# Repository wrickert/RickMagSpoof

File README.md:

This is my variant of the MagSpoof Project

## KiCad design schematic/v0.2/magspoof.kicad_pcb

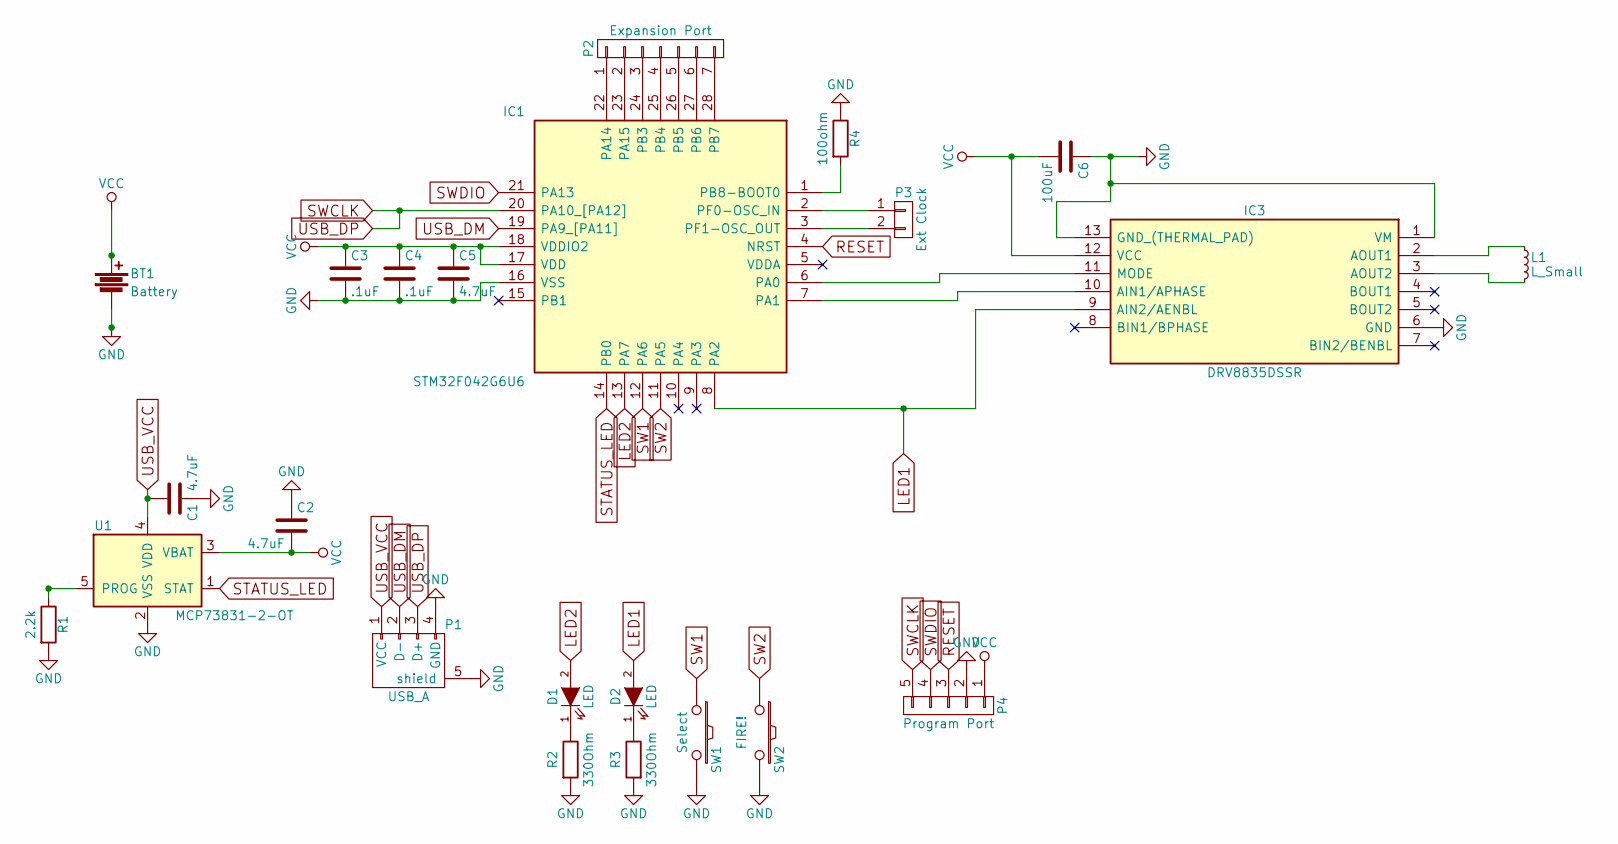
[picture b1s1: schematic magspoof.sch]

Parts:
BT1: Battery; Pin_Header_Straight_1x02_Pitch2.54mm
C1, C2, C5: 4.7uF; C_0805_HandSoldering
C3, C4: .1uF; C_0805_HandSoldering
C6: 100uF; C_1206
D1, D2: LED; LED_0805
IC1: STM32F042G6U6; QFN50P400X400X60-28N; Manufacturer_Part_Number STM32F042G6U6
IC3: DRV8835DSSR; SON50P200X300X80-13N; Manufacturer_Part_Number DRV8835DSSR
L1: L_Small; Pin_Header_Straight_1x02_Pitch2.54mm
P1: USB_A; usb-PCB
P2: Expansion Port; Socket_Strip_Straight_1x07_Pitch2.54mm
P3: Ext Clock; Pin_Header_Straight_1x02_Pitch2.54mm
P4: Program Port; Pin_Header_Straight_1x05_Pitch2.54mm
R1: 2.2k; R_0805
R2, R3: 330Ohm; R_0805
R4: 100ohm; R_0805
SW1: Select; TACTILE_SWITCH_SMD_6.2MM_TALL
SW2: FIRE!; TACTILE_SWITCH_SMD_6.2MM_TALL
U1: MCP73831-2-OT; SOT-23-5

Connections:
GND: BT1.2, C1.1, C2.1, C3.2, C4.2, C5.2, C6.1, IC1.16 (VSS), IC3.1 (VM), IC3.6 (GND), IC3.13 (GND_(THERMAL_PAD)), P1.4 (GND), P1.5 (shield), P4.2, R1.2, R2.2, R3.2, R4.1, SW1.2, SW2.2, U1.2 (VSS); also elsewhere on the board
LED1: D2.2 (A), IC1.8 (PA2), IC3.9 (AIN2/AENBL)
LED2: D1.2 (A), IC1.13 (PA7)
unnamed: D1.1 (K), R2.1
unnamed: D2.1 (K), R3.1
unnamed: IC1.1 (PB8-BOOT0), R4.2
unnamed: IC1.2 (PF0-OSC_IN), P3.1
unnamed: IC1.3 (PF1-OSC_OUT), P3.2
unnamed: IC1.6 (PA0), IC3.11 (MODE)
unnamed: IC1.7 (PA1), IC3.10 (AIN1/APHASE)
unnamed: IC1.22 (PA14), P2.1
unnamed: IC1.23 (PA15), P2.2
unnamed: IC1.24 (PB3), P2.3
unnamed: IC1.25 (PB4), P2.4
unnamed: IC1.26 (PB5), P2.5
unnamed: IC1.27 (PB6), P2.6
unnamed: IC1.28 (PB7), P2.7
unnamed: IC3.2 (AOUT1), L1.1
unnamed: IC3.3 (AOUT2), L1.2
unnamed: R1.1, U1.5 (PROG)
RESET: IC1.4 (NRST), P4.3
STATUS_LED: IC1.14 (PB0), U1.1 (STAT)
SW1: IC1.12 (PA6), SW1.1; also elsewhere on the board
SW2: IC1.11 (PA5), SW2.1; also elsewhere on the board
SWCLK: IC1.20 (PA10_[PA12]), P1.3 (D+), P4.5
SWDIO: IC1.21 (PA13), P4.4
USB_DM: IC1.19 (PA9_[PA11]), P1.2 (D-)
USB_VCC: C1.2, P1.1 (VCC), U1.4 (VDD)
VCC: BT1.1, C2.2, C3.1, C4.1, C5.1, C6.2, IC1.17 (VDD), IC1.18 (VDDIO2), IC3.12 (VCC), P4.1, U1.3 (VBAT)

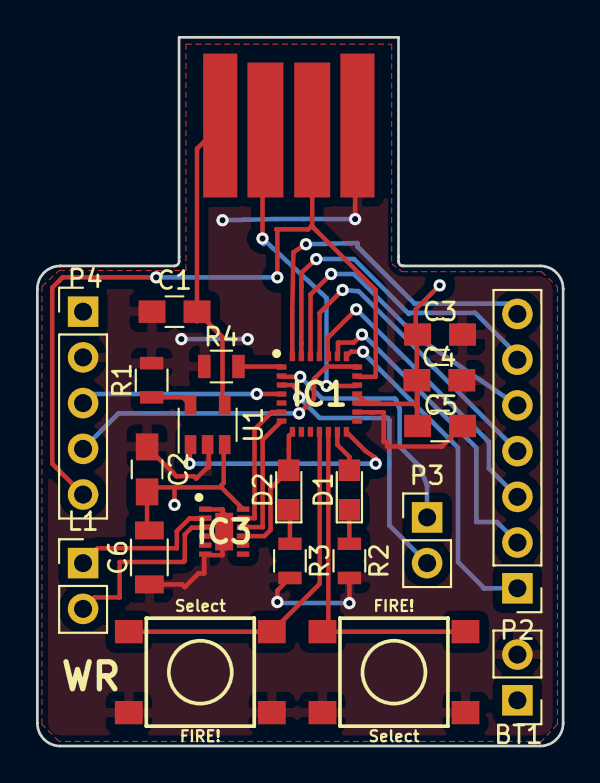
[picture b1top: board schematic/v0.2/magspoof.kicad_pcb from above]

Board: 2 copper layers, 29.2 x 39.4 mm, 23 parts (0 on the bottom side), 29 nets.

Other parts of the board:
FIRE!: Select; TACTILE_SWITCH_SMD_6.2MM_TALL
Select: FIRE!; TACTILE_SWITCH_SMD_6.2MM_TALL

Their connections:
GND: FIRE!.B1, FIRE!.B2, Select.B1, Select.B2; also elsewhere on the board
SW1: Select.A1, Select.A2; also elsewhere on the board
SW2: FIRE!.A1, FIRE!.A2; also elsewhere on the board

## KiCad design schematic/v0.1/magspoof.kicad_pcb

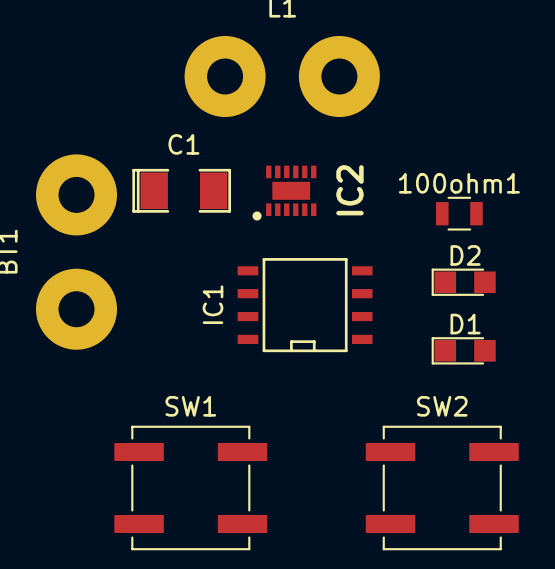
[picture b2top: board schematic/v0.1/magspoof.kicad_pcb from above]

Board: 2 copper layers, 10 parts (0 on the bottom side), 10 nets, no tracks yet.

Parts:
100ohm1: R1; R_0805
BT1: 3.7v LiPo; SolderWirePad_2x_2mmDrill
C1: 100uF; SMD-1206_Pol
D1, D2: LED; LED_0805
IC1: ATTINY85-S; SOIC-8-N
IC2: DRV8835DSSR; SON50P200X300X80-13N
L1: Coil; SolderWirePad_2x_2mmDrill
SW1: Fire!; SW_SPST_B3SL-1002P
SW2: Select; SW_SPST_B3SL-1002P

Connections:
unnamed: 100ohm1.1, D1.1, D2.1
unnamed: 100ohm1.2, C1.2, IC1.4, IC2.6, IC2.13, SW1.2, SW2.2
unnamed: BT1.1, C1.1, IC1.8, IC2.1, IC2.12
unnamed: D1.2, IC1.2, IC2.9
unnamed: D2.2, IC1.3
unnamed: IC1.1, SW2.1
unnamed: IC1.5, IC2.10
unnamed: IC1.6, IC2.11
unnamed: IC1.7, SW1.1
unnamed: IC2.2, L1.1

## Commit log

2017-12-20 Initial commit, just about to start traces so I want a snapshot so I can revert to this state in the likely case that I mess up
2017-12-20 Added readme
2017-12-20 Changed stm32 footprint
2017-12-21 Completed traces on v2
2017-12-21 Completed traces on v2 --trying to make things neater without destroying everything
2017-12-21 PCB ordered
